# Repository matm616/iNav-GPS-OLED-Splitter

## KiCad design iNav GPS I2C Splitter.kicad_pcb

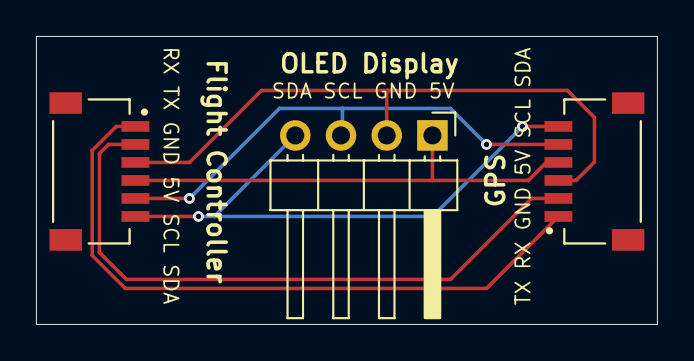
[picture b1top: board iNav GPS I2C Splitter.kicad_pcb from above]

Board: 2 copper layers, 34.5 x 16.0 mm, 3 parts (0 on the bottom side), 6 nets.

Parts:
Flight Controller: SM06B-SRSS-TB_LF__SN_; JST_SM06B-SRSS-TB_LF__SN_
GPS: SM06B-SRSS-TB_LF__SN_; JST_SM06B-SRSS-TB_LF__SN_
OLED Display: Conn_01x04; PinHeader_1x04_P2.54mm_Horizontal

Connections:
/5V: Flight Controller.4, GPS.4, OLED Display.1
/GND: Flight Controller.3, GPS.3, OLED Display.2
/RX: Flight Controller.1, GPS.1
/SCL: Flight Controller.5, GPS.5, OLED Display.3
/SDA: Flight Controller.6, GPS.6, OLED Display.4
/TX: Flight Controller.2, GPS.2

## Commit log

2025-12-05 Create .gitignore for KiCad project
    Add a .gitignore file for KiCad project files
2025-12-05 Added project files
2025-12-05 Updated silkscreening for OLED pins
